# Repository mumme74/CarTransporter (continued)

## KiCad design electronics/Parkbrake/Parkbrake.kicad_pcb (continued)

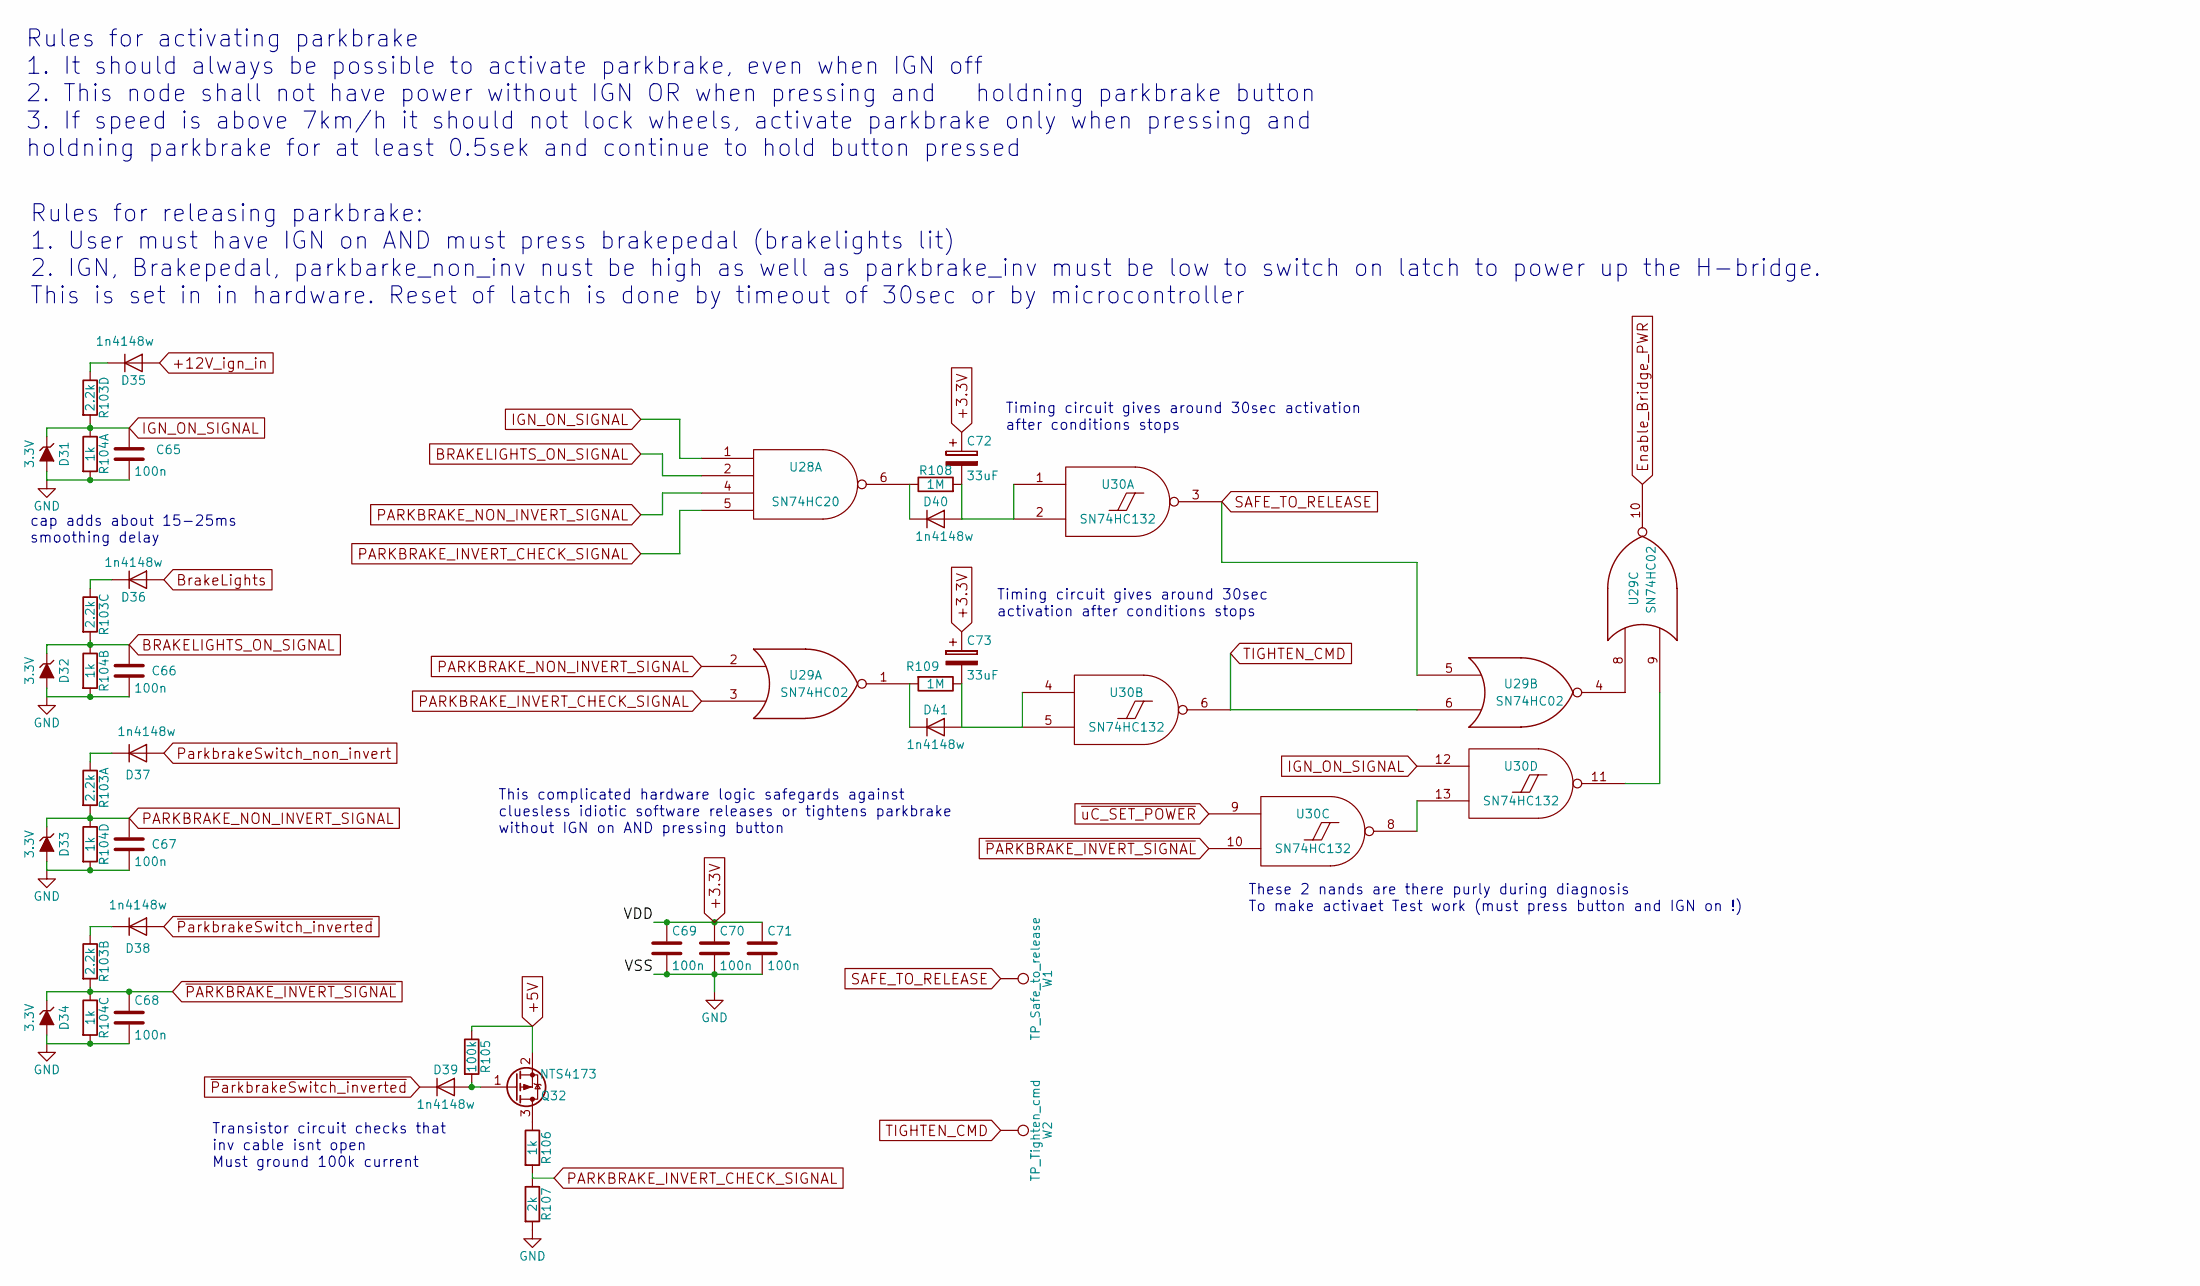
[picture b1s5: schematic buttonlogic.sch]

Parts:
C65, C66, C67, C68, C69, C70, C71: 100n; C_0805; part 0805B104J500CT; farnell 2496940
C72, C73: 33uF; CP_1206; part 293D336X96R3A2TE3; farnell 1754149
D31, D32, D33, D34: 3.3V; SOD-323; part MM3Z3V3ST1G; farnell 2463489
D35, D36, D37, D38, D39, D40, D41: 1n4148w; SOD-323; part 1N4148WS; farnell 1466524
Q32: NTS4173; SOT-323; part NTS4173PT1G; farnell 2533203
R103: 2.2k; R_Array_Concave_4x0603; part EXB38V222JV; farnell 2060102
R104: 1k; R_Array_Concave_4x0603; part EXB38V102JV; farnell 2060100
R105: 100k; R_0805; part MC01W08051100K; farnell 9332405
R106: 1k; R_0805; part MC01W080511K; farnell 9332383
R107: 2k; R_0805; part MC01W080512K; farnell 9332766
R108, R109: 1M; R_0805; part MC01W080511M; farnell 9332413
U28: SN74HC20; TSSOP-14_4.4x5mm_Pitch0.65mm; part SN74HC20PW; farnell 1741207
U29: SN74HC02; TSSOP-14_4.4x5mm_Pitch0.65mm; part SN74HC02PWR; farnell 9590927
U30: SN74HC132; TSSOP-14_4.4x5mm_Pitch0.65mm; part SN74HC132PWR; farnell 2342491
W1: TP_Safe_to_release; Measurement_Point_Round-SMD-Pad_Small
W2: TP_Tighten_cmd; Measurement_Point_Round-SMD-Pad_Small

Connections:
+3.3V: C69.1, C70.1, C71.1, C72.1, C73.1, U28.14 (VCC), U29.14 (VCC), U30.14 (VCC); also elsewhere on the board
+5V: Q32.2 (S), R105.1; also elsewhere on the board
+12V_ign_in: D35.2 (A); also elsewhere on the board
BRAKELIGHTS_ON_SIGNAL: C66.1, D32.1 (K), R103.6, R104.2, U28.2; also elsewhere on the board
BrakeLights: D36.2 (A); also elsewhere on the board
Enable_Bridge_PWR: U29.10; also elsewhere on the board
IGN_ON_SIGNAL: C65.1, D31.1 (K), R103.5, R104.1, U28.1, U30.12; also elsewhere on the board
LR_wheelsensor_in-: C65.2, C66.2, C67.2, C68.2, C69.2, C70.2, C71.2, D31.2 (A), D32.2 (A), D33.2 (A), D34.2 (A), R104.5, R104.6, R104.7, R104.8, R107.2, U28.7 (GND), U29.7 (GND), U30.7 (GND); also elsewhere on the board
unnamed: C72.2, D40.2 (A), R108.2, U30.1, U30.2
unnamed: C73.2, D41.2 (A), R109.1, U30.4, U30.5
unnamed: D35.1 (K), R103.4
unnamed: D36.1 (K), R103.3
unnamed: D37.1 (K), R103.1
unnamed: D38.1 (K), R103.2
unnamed: D39.2 (A), Q32.1 (G), R105.2
unnamed: D40.1 (K), R108.1, U28.6
unnamed: D41.1 (K), R109.2, U29.1
unnamed: Q32.3 (D), R106.1
unnamed: U29.4, U29.8
unnamed: U29.9, U30.11
unnamed: U30.8, U30.13
PARKBRAKE_INVERT_CHECK_SIGNAL: R106.2, R107.1, U28.5, U29.3
PARKBRAKE_NON_INVERT_SIGNAL: C67.1, D33.1 (K), R103.8, R104.4, U28.4, U29.2; also elsewhere on the board
ParkbrakeSwitch_non_invert: D37.2 (A); also elsewhere on the board
SAFE_TO_RELEASE: U29.5, U30.3, W1.1; also elsewhere on the board
TIGHTEN_CMD: U29.6, U30.6, W2.1; also elsewhere on the board
~PARKBRAKE_INVERT_SIGNAL: C68.1, D34.1 (K), R103.7, R104.3, U30.10; also elsewhere on the board
~ParkbrakeSwitch_inverted: D38.2 (A), D39.1 (K); also elsewhere on the board
~uC_SET_POWER: U30.9; also elsewhere on the board

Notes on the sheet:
Rules for activating parkbrake 1. It should always be possible to activate parkbrake, even when IGN off 2. This node shall not have power without IGN OR when pressing and holdning parkbrake button 3. If speed is above 7km/h it should not lock wheels, activate parkbrake only when pressing and holdni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
Rules for releasing parkbrake: 1. User must have IGN on AND must press brakepedal (brakelights lit) 2. IGN, Brakepedal, parkbarke_non_inv nust be high as well as parkbrake_inv must be low to switch on latch to power up the H-bridge. This is set in in hardware. Reset of latch is done by timeout of 3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
cap adds about 15-25ms smoothing delay
Transistor circuit checks that inv cable isnt open Must ground 100k current
Timing circuit gives around 30sec activation after conditions stops
Timing circuit gives around 30sec activation after conditions stops
This complicated hardware logic safegards against cluesless idiotic software releases or tightens parkbrake without IGN on AND pressing button
These 2 nands are there purly during diagnosis To make activaet Test work (must press button and IGN on !)

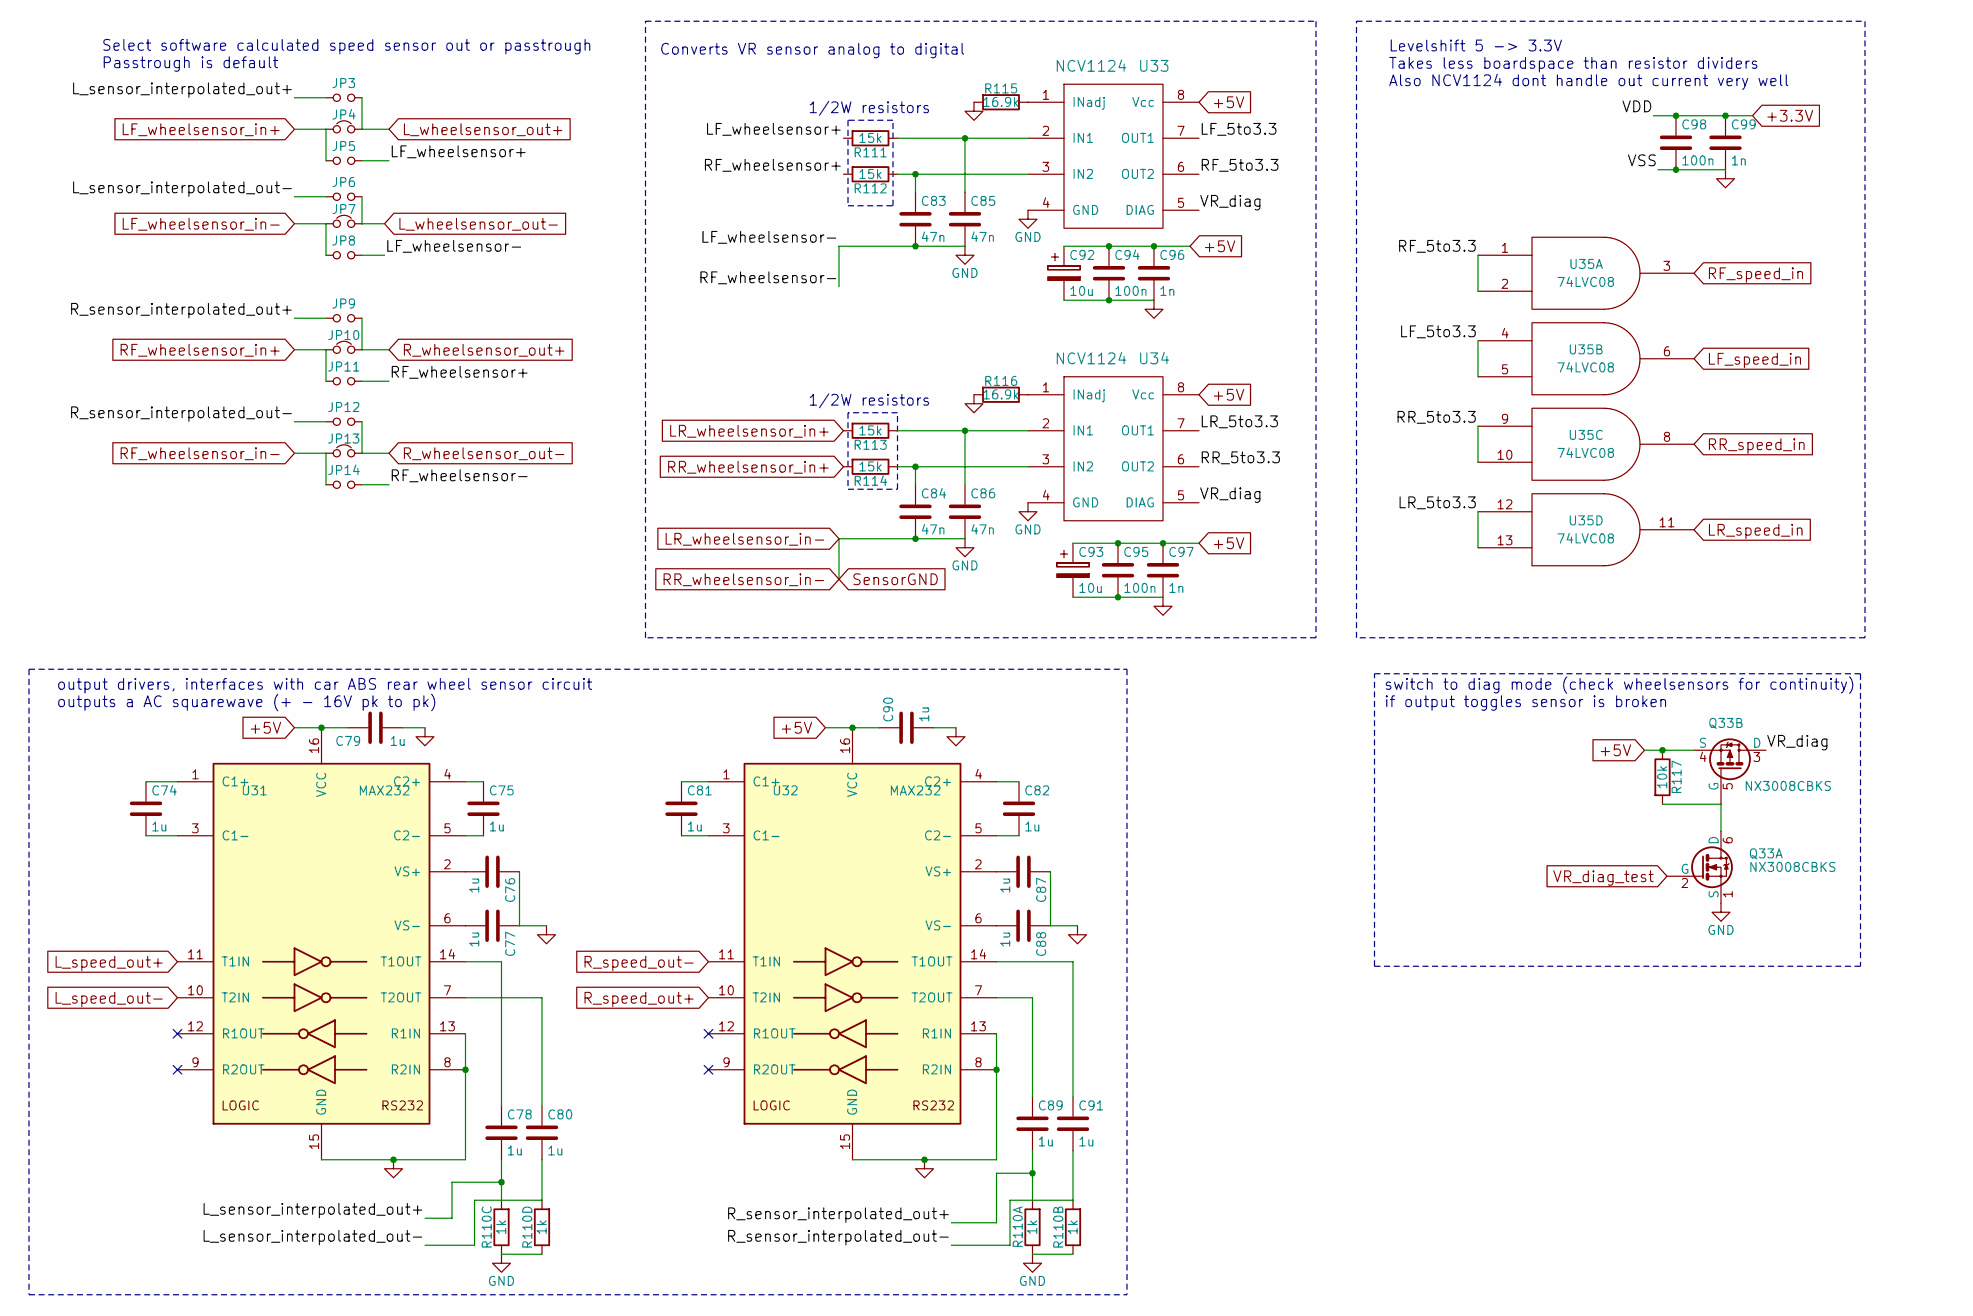
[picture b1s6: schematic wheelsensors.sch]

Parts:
C74, C75, C76, C77, C78, C79, C80, C81, C82, C87, C88, C89, C90, C91: 1u; C_1206; part GRM31MR71E105JA01L; farnell 2362126
C83, C84, C85, C86: 47n; C_0805; part 0805B473J500CT; farnell 2496981
C92, C93: 10u; CP_0805; part TMCP0J106KTRF; farnell 2491430
C94, C95, C98: 100n; C_0805; part 0805B104J500CT; farnell 2496940
C96, C97, C99: 1n; C_0805; part GRM2165C1H102JA01D; farnell 2494247
JP3: soft_L_out+; R_0805_HandSoldering; part RC1206JR-070RL; farnell 9240276
JP4: L_passth+; R_0805_HandSoldering; part RC1206JR-070RL; farnell 9240276
JP5: LF+_to_in; R_0805_HandSoldering; part RC1206JR-070RL; farnell 9240276
JP6: soft_L_out-; R_0805_HandSoldering; part RC1206JR-070RL; farnell 9240276
JP7: L_passth-; R_0805_HandSoldering; part RC1206JR-070RL; farnell 9240276
JP8: LF-_to_in; R_0805_HandSoldering; part RC1206JR-070RL; farnell 9240276
JP9: soft_R_out+; R_0805_HandSoldering; part RC1206JR-070RL; farnell 9240276
JP10: RF_passth+; R_0805_HandSoldering; part RC1206JR-070RL; farnell 9240276
JP11: RF+_to_in; R_0805_HandSoldering; part RC1206JR-070RL; farnell 9240276
JP12: soft_R_out-; R_0805_HandSoldering; part RC1206JR-070RL; farnell 9240276
JP13: RF_passth-; R_0805_HandSoldering; part RC1206JR-070RL; farnell 9240276
JP14: RF-_to_in; R_0805_HandSoldering; part RC1206JR-070RL; farnell 9240276
Q33: NX3008CBKS; SOT-363; part NX3008CBKS; farnell 2069539
R110: 1k; R_Array_Concave_4x0603; part EXB38V102JV; farnell 2060100
R111, R112, R113, R114: 15k; R_0805; part ERJP06F1502V; farnell 1750772
R115, R116: 16.9k; R_0805; part MC01W0805116K9; farnell 2141858
R117: 10k; R_0805; part MC01W0805110K; farnell 9332391
U31, U32: MAX232; TSSOP-16_4.4x5mm_Pitch0.65mm; part MAX202IPW; farnell 2335478
U33, U34: NCV1124; SOIC-8_3.9x4.9mm_Pitch1.27mm; part NCV1124DR2G; farnell 2534601
U35: 74LVC08; TSSOP-14_4.4x5mm_Pitch0.65mm; part 74LVC08APW-Q100.11; farnell 2445097

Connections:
+3.3V: C98.1, C99.1, U35.14 (VCC); also elsewhere on the board
+5V: C79.1, C90.1, C92.1, C93.1, C94.1, C95.1, C96.1, C97.1, Q33.4 (S), R117.1, U31.16 (VCC), U32.16 (VCC), U33.8 (Vcc), U34.8 (Vcc); also elsewhere on the board
/Wheelsensors/LF_5to3.3: U33.7 (OUT1), U35.4, U35.5
/Wheelsensors/LF_wheelsensor+: JP5.2, R111.2
/Wheelsensors/LR_5to3.3: U34.7 (OUT1), U35.12, U35.13
/Wheelsensors/L_sensor_interpolated_out+: C78.2, JP3.1, R110.6
/Wheelsensors/L_sensor_interpolated_out-: C80.2, JP6.1, R110.5
/Wheelsensors/RF_5to3.3: U33.6 (OUT2), U35.1, U35.2
/Wheelsensors/RF_wheelsensor+: JP11.2, R112.2
/Wheelsensors/RR_5to3.3: U34.6 (OUT2), U35.9, U35.10
/Wheelsensors/R_sensor_interpolated_out+: C89.2, JP9.1, R110.8
/Wheelsensors/R_sensor_interpolated_out-: C91.2, JP12.1, R110.7
/Wheelsensors/VR_diag: Q33.3 (D), U33.5 (DIAG), U34.5 (DIAG)
LF_speed_in: U35.6; also elsewhere on the board
LF_wheelsensor_in+: JP4.1, JP5.1; also elsewhere on the board
LF_wheelsensor_in-: JP7.1, JP8.1; also elsewhere on the board
LR_speed_in: U35.11; also elsewhere on the board
LR_wheelsensor_in+: R113.2; also elsewhere on the board
LR_wheelsensor_in-: C76.1, C77.1, C79.2, C83.2, C84.2, C85.2, C86.2, C87.1, C88.1, C90.2, C92.2, C93.2, C94.2, C95.2, C96.2, C97.2, C98.2, C99.2, JP8.2, JP14.2, Q33.1 (S), R110.1, R110.2, R110.3, R110.4, R115.2, R116.2, U31.8 (R2IN), U31.13 (R1IN), U31.15 (GND), U32.8 (R2IN), U32.13 (R1IN), U32.15 (GND), U33.4 (GND), U34.4 (GND), U35.7 (GND); also elsewhere on the board
L_speed_out+: U31.11 (T1IN); also elsewhere on the board
L_speed_out-: U31.10 (T2IN); also elsewhere on the board
L_wheelsensor_out+: JP3.2, JP4.2; also elsewhere on the board
L_wheelsensor_out-: JP6.2, JP7.2; also elsewhere on the board
unnamed: C74.1, U31.1 (C1+)
unnamed: C74.2, U31.3 (C1-)
unnamed: C75.1, U31.4 (C2+)
unnamed: C75.2, U31.5 (C2-)
unnamed: C76.2, U31.2 (VS+)
unnamed: C77.2, U31.6 (VS-)
unnamed: C78.1, U31.14 (T1OUT)
unnamed: C80.1, U31.7 (T2OUT)
unnamed: C81.1, U32.1 (C1+)
unnamed: C81.2, U32.3 (C1-)
unnamed: C82.1, U32.4 (C2+)
unnamed: C82.2, U32.5 (C2-)
unnamed: C83.1, R112.1, U33.3 (IN2)
unnamed: C84.1, R114.1, U34.3 (IN2)
unnamed: C85.1, R111.1, U33.2 (IN1)
unnamed: C86.1, R113.1, U34.2 (IN1)
unnamed: C87.2, U32.2 (VS+)
unnamed: C88.2, U32.6 (VS-)
unnamed: C89.1, U32.7 (T2OUT)
unnamed: C91.1, U32.14 (T1OUT)
unnamed: Q33.5 (G), Q33.6 (D), R117.2
unnamed: R115.1, U33.1 (INadj)
unnamed: R116.1, U34.1 (INadj)
RF_speed_in: U35.3; also elsewhere on the board
RF_wheelsensor_in+: JP10.1, JP11.1; also elsewhere on the board
RF_wheelsensor_in-: JP13.1, JP14.1; also elsewhere on the board
RR_speed_in: U35.8; also elsewhere on the board
RR_wheelsensor_in+: R114.2; also elsewhere on the board
R_speed_out+: U32.10 (T2IN); also elsewhere on the board
R_speed_out-: U32.11 (T1IN); also elsewhere on the board
R_wheelsensor_out+: JP9.2, JP10.2; also elsewhere on the board
R_wheelsensor_out-: JP12.2, JP13.2; also elsewhere on the board
VR_diag_test: Q33.2 (G); also elsewhere on the board

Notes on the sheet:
Select software calculated speed sensor out or passtrough Passtrough is default
1/2W resistors
output drivers, interfaces with car ABS rear wheel sensor circuit outputs a AC squarewave (+ - 16V pk to pk)
Converts VR sensor analog to digital
switch to diag mode (check wheelsensors for continuity) if output toggles sensor is broken
Levelshift 5 -> 3.3V Takes less boardspace than resistor dividers Also NCV1124 dont handle out current very well

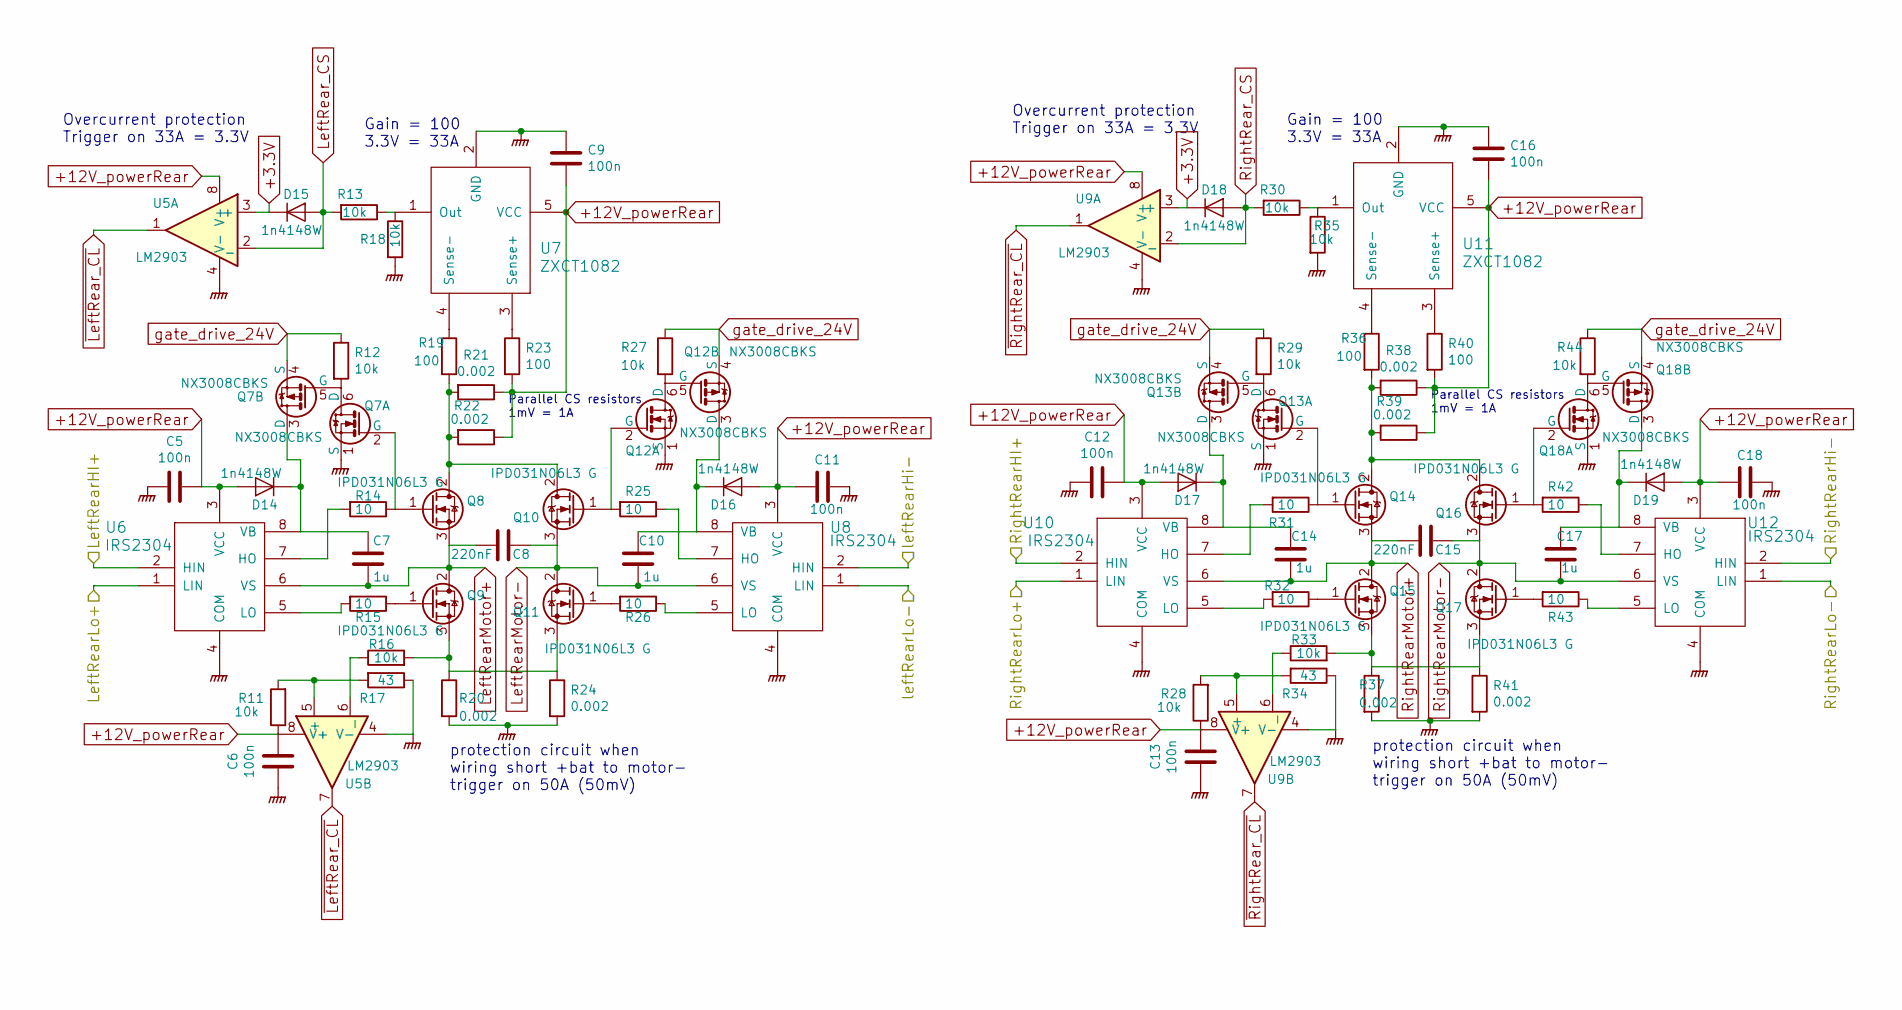
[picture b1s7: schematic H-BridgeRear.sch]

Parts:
C5, C6, C9, C11, C12, C13, C16, C18: 100n; C_0805; part 0805B104J500CT; farnell 2496940
C7, C10, C14, C17: 1u; C_1206; part GRM31MR71E105JA01L; farnell 2362126
C8, C15: 220nF; C_1206; part 1206B224J500CT; farnell 2497088
D14, D15, D16, D17, D18, D19: 1n4148W; SOD-323; part 1N4148WS; farnell 1466524
Q7, Q12, Q13, Q18: NX3008CBKS; SOT-363; part NX3008CBKS; farnell 2069539
Q8, Q9, Q10, Q11, Q14, Q15, Q16, Q17: IPD031N06L3 G; TO-252-2Lead; part IPD031N06L3 G; farnell 2480814
R11, R12, R13, R16, R18, R27, R28, R29, R30, R33, R35, R44: 10k; R_0805; part MC01W0805110K; farnell 9332391
R14, R15, R25, R26, R31, R32, R42, R43: 10; R_0805; part WF08P10R0FTL; farnell 2502783
R17, R34: 43; R_0805; part MC01W0805143R; farnell 9333240
R19, R23, R36, R40: 100; R_0805; part MC01W08051100R; farnell 9332375
R20, R21, R22, R24, R37, R38, R39, R41: 0.002; R_1206; part ULR1S-R002FT2; farnell 1621962
U5, U9: LM2903; TSSOP-8_4.4x3mm_Pitch0.65mm; part LM2903PT; farnell 1094243
U6, U8, U10, U12: IRS2304; SOIC-8_3.9x4.9mm_Pitch1.27mm; part IRS2304SPBF; farnell 1498208
U7, U11: ZXCT1082; SOT-23-5; part ZXCT1082E5TA; farnell 1904025

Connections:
+3.3V: D15.1 (K), D18.1 (K), U5.3 (+), U9.3 (+); also elsewhere on the board
+12V_powerRear: C5.1, C6.1, C9.2, C11.2, C12.1, C13.1, C16.2, C18.2, D14.2 (A), D16.2 (A), D17.2 (A), D19.2 (A), R11.1, R21.1, R22.1, R23.2, R28.1, R38.1, R39.1, R40.2, U5.8 (V+), U6.3 (VCC), U7.5 (VCC), U8.3 (VCC), U9.8 (V+), U10.3 (VCC), U11.5 (VCC), U12.3 (VCC); also elsewhere on the board
/H-Bridge_logic/H-BridgeRear/LeftRearHI+: U6.2 (HIN), U8.1 (LIN); also elsewhere on the board
/H-Bridge_logic/H-BridgeRear/LeftRearLo+: U6.1 (LIN), U8.2 (HIN); also elsewhere on the board
/H-Bridge_logic/H-BridgeRear/RightRearHI+: U10.2 (HIN), U12.1 (LIN); also elsewhere on the board
/H-Bridge_logic/H-BridgeRear/RightRearHi-: U10.1 (LIN), U12.2 (HIN); also elsewhere on the board
GNDPWR: C5.2, C6.2, C9.1, C11.1, C12.2, C13.2, C16.1, C18.1, Q7.1 (S), Q12.1 (S), Q13.1 (S), Q18.1 (S), R17.1, R18.2, R20.2, R24.2, R34.1, R35.2, R37.2, R41.2, U5.4 (V-), U6.4 (COM), U7.2 (GND), U8.4 (COM), U9.4 (V-), U10.4 (COM), U11.2 (GND), U12.4 (COM); also elsewhere on the board
LeftRearMotor+: C7.1, C8.2, Q8.3 (S), Q9.2 (D), U6.6 (VS); also elsewhere on the board
LeftRearMotor-: C8.1, C10.1, Q10.3 (S), Q11.2 (D), U8.6 (VS); also elsewhere on the board
LeftRear_CS: D15.2 (A), R13.2, U5.2 (_); also elsewhere on the board
unnamed: C7.2, D14.1 (K), Q7.3 (D), U6.8 (VB)
unnamed: C10.2, D16.1 (K), Q12.3 (D), U8.8 (VB)
unnamed: C14.2, D17.1 (K), Q13.3 (D), U10.8 (VB)
unnamed: C17.1, D19.1 (K), Q18.3 (D), U12.8 (VB)
unnamed: Q7.2 (G), Q8.1 (G), R14.1
unnamed: Q7.5 (G), Q7.6 (D), R12.2
unnamed: Q9.1 (G), R15.1
unnamed: Q10.1 (G), Q12.2 (G), R25.2
unnamed: Q8.2 (D), Q10.2 (D), R19.2, R21.2, R22.2
unnamed: Q11.1 (G), R26.2
unnamed: Q9.3 (S), Q11.3 (S), R16.2, R20.1, R24.1
unnamed: Q12.5 (G), Q12.6 (D), R27.2
unnamed: Q13.2 (G), Q14.1 (G), R31.1
unnamed: Q13.5 (G), Q13.6 (D), R29.2
unnamed: Q14.2 (D), Q16.2 (D), R36.2, R38.2, R39.2
unnamed: Q15.1 (G), R32.1
unnamed: Q15.3 (S), Q17.3 (S), R33.2, R37.1, R41.1
unnamed: Q16.1 (G), Q18.2 (G), R42.2
unnamed: Q17.1 (G), R43.2
unnamed: Q18.5 (G), Q18.6 (D), R44.2
unnamed: R11.2, R17.2, U5.5 (+)
unnamed: R13.1, R18.1, U7.1 (Out)
unnamed: R14.2, U6.7 (HO)
unnamed: R15.2, U6.5 (LO)
unnamed: R16.1, U5.6 (_)
unnamed: R19.1, U7.4 (Sense-)
unnamed: R23.1, U7.3 (Sense+)
unnamed: R25.1, U8.7 (HO)
unnamed: R26.1, U8.5 (LO)
unnamed: R28.2, R34.2, U9.5 (+)
unnamed: R30.1, R35.1, U11.1 (Out)
unnamed: R31.2, U10.7 (HO)
unnamed: R32.2, U10.5 (LO)
unnamed: R33.1, U9.6 (_)
unnamed: R36.1, U11.4 (Sense-)
unnamed: R40.1, U11.3 (Sense+)
unnamed: R42.1, U12.7 (HO)
unnamed: R43.1, U12.5 (LO)
RightRearMotor+: C14.1, C15.2, Q14.3 (S), Q15.2 (D), U10.6 (VS); also elsewhere on the board
RightRearMotor-: C15.1, C17.2, Q16.3 (S), Q17.2 (D), U12.6 (VS); also elsewhere on the board
RightRear_CS: D18.2 (A), R30.2, U9.2 (_); also elsewhere on the board
gate_drive_24V: Q7.4 (S), Q12.4 (S), Q13.4 (S), Q18.4 (S), R12.1, R27.1, R29.1, R44.1; also elsewhere on the board
~LeftRear_CL: U5.1, U5.7; also elsewhere on the board
~RightRear_CL: U9.1, U9.7; also elsewhere on the board

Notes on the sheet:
Parallel CS resistors 1mV = 1A
protection circuit when wiring short +bat to motor- trigger on 50A (50mV)
Gain = 100 3.3V = 33A
Overcurrent protection Trigger on 33A = 3.3V

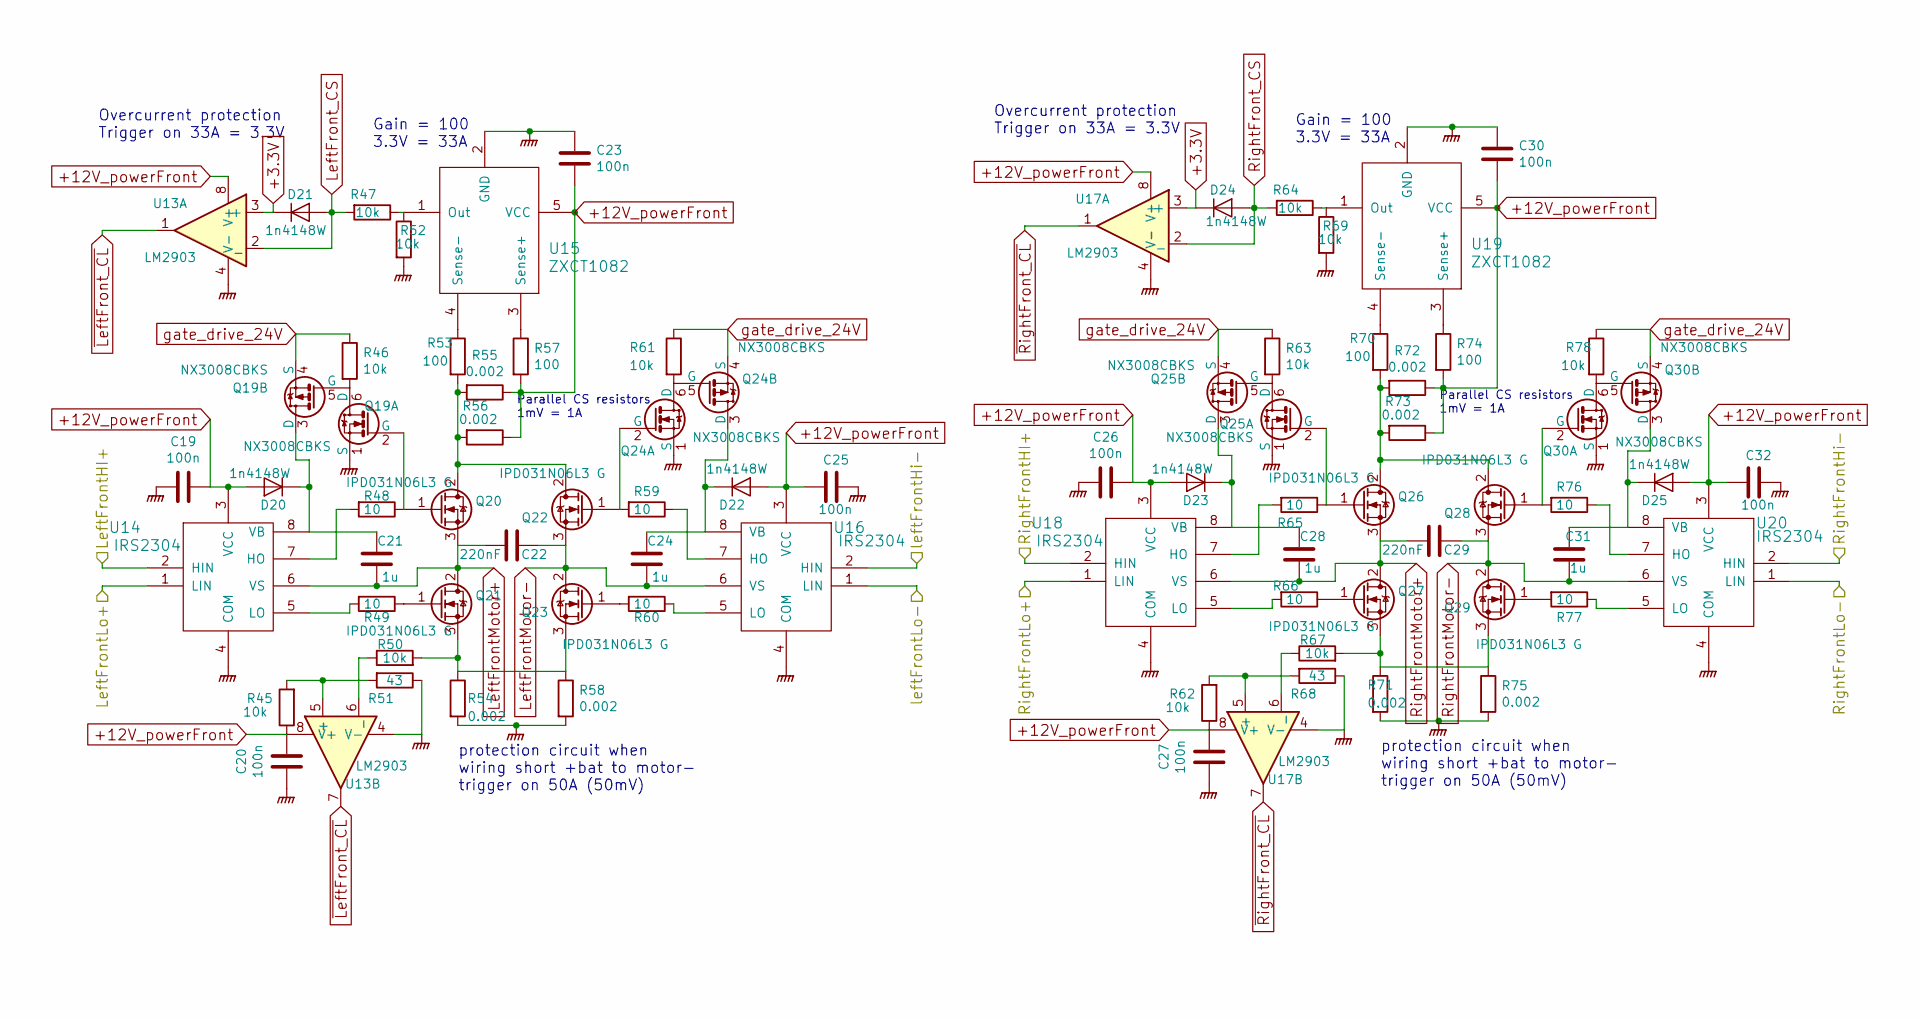
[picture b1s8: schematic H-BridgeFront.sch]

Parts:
C19, C20, C23, C25, C26, C27, C30, C32: 100n; C_0805; part 0805B104J500CT; farnell 2496940
C21, C24, C28, C31: 1u; C_1206; part GRM31MR71E105JA01L; farnell 2362126
C22, C29: 220nF; C_1206; part 1206B224J500CT; farnell 2497088
D20, D21, D22, D25: 1n4148W; SOD-323; part 1N4148WS; farnell 1466524
D23, D24: 1n4148W; SOD-323; part 1N4148WS; farnell 2433353
Q19, Q24, Q25, Q30: NX3008CBKS; SOT-363; part NX3008CBKS; farnell 2069539
Q20, Q21, Q22, Q23, Q26, Q27, Q28, Q29: IPD031N06L3 G; TO-252-2Lead; part IPD031N06L3 G; farnell 2480814
R45, R46, R47, R50, R52, R61, R62, R63, R64, R67, R69, R78: 10k; R_0805; part MC01W0805110K; farnell 9332391
R48, R49, R59, R60, R65, R66, R76, R77: 10; R_0805; part WF08P10R0FTL; farnell 2502783
R51, R68: 43; R_0805; part MC01W0805143R; farnell 9333240
R53, R57, R70, R74: 100; R_0805; part MC01W08051100R; farnell 9332375
R54, R55, R56, R58, R71, R72, R73, R75: 0.002; R_1206; part ULR1S-R002FT2; farnell 1621962
U13, U17: LM2903; TSSOP-8_4.4x3mm_Pitch0.65mm; part LM2903PT; farnell 1094243
U14, U16, U18, U20: IRS2304; SOIC-8_3.9x4.9mm_Pitch1.27mm; part IRS2304SPBF; farnell 1498208
U15, U19: ZXCT1082; SOT-23-5; part ZXCT1082E5TA; farnell 1904025

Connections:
+3.3V: D21.1 (K), D24.1 (K), U13.3 (+), U17.3 (+); also elsewhere on the board
+12V_powerFront: C19.1, C20.1, C23.2, C25.2, C26.1, C27.1, C30.2, C32.2, D20.2 (A), D22.2 (A), D23.2 (A), D25.2 (A), R45.1, R55.1, R56.1, R57.2, R62.1, R72.1, R73.1, R74.2, U13.8 (V+), U14.3 (VCC), U15.5 (VCC), U16.3 (VCC), U17.8 (V+), U18.3 (VCC), U19.5 (VCC), U20.3 (VCC); also elsewhere on the board
/H-Bridge_logic/H-BridgeFront/LeftFrontHI+: U14.2 (HIN), U16.1 (LIN); also elsewhere on the board
/H-Bridge_logic/H-BridgeFront/LeftFrontLo+: U14.1 (LIN), U16.2 (HIN); also elsewhere on the board
/H-Bridge_logic/H-BridgeFront/RightFrontHI+: U18.2 (HIN), U20.1 (LIN); also elsewhere on the board
/H-Bridge_logic/H-BridgeFront/RightFrontHi-: U18.1 (LIN), U20.2 (HIN); also elsewhere on the board
GNDPWR: C19.2, C20.2, C23.1, C25.1, C26.2, C27.2, C30.1, C32.1, Q19.1 (S), Q24.1 (S), Q25.1 (S), Q30.1 (S), R51.1, R52.2, R54.2, R58.2, R68.1, R69.2, R71.2, R75.2, U13.4 (V-), U14.4 (COM), U15.2 (GND), U16.4 (COM), U17.4 (V-), U18.4 (COM), U19.2 (GND), U20.4 (COM); also elsewhere on the board
LeftFrontMotor+: C21.1, C22.2, Q20.3 (S), Q21.2 (D), U14.6 (VS); also elsewhere on the board
LeftFrontMotor-: C22.1, C24.1, Q22.3 (S), Q23.2 (D), U16.6 (VS); also elsewhere on the board
LeftFront_CS: D21.2 (A), R47.2, U13.2 (_); also elsewhere on the board
unnamed: C21.2, D20.1 (K), Q19.3 (D), U14.8 (VB)
unnamed: C24.2, D22.1 (K), Q24.3 (D), U16.8 (VB)
unnamed: C28.2, D23.1 (K), Q25.3 (D), U18.8 (VB)
unnamed: C31.1, D25.1 (K), Q30.3 (D), U20.8 (VB)
unnamed: Q19.2 (G), Q20.1 (G), R48.1
unnamed: Q19.5 (G), Q19.6 (D), R46.2
unnamed: Q20.2 (D), Q22.2 (D), R53.2, R55.2, R56.2
unnamed: Q21.1 (G), R49.1
unnamed: Q21.3 (S), Q23.3 (S), R50.2, R54.1, R58.1
unnamed: Q22.1 (G), Q24.2 (G), R59.2
unnamed: Q23.1 (G), R60.2
unnamed: Q24.5 (G), Q24.6 (D), R61.2
unnamed: Q25.2 (G), Q26.1 (G), R65.1
unnamed: Q25.5 (G), Q25.6 (D), R63.2
unnamed: Q26.2 (D), Q28.2 (D), R70.2, R72.2, R73.2
unnamed: Q27.1 (G), R66.1
unnamed: Q27.3 (S), Q29.3 (S), R67.2, R71.1, R75.1
unnamed: Q28.1 (G), Q30.2 (G), R76.2
unnamed: Q29.1 (G), R77.2
unnamed: Q30.5 (G), Q30.6 (D), R78.2
unnamed: R45.2, R51.2, U13.5 (+)
unnamed: R47.1, R52.1, U15.1 (Out)
unnamed: R48.2, U14.7 (HO)
unnamed: R49.2, U14.5 (LO)
unnamed: R50.1, U13.6 (_)
unnamed: R53.1, U15.4 (Sense-)
unnamed: R57.1, U15.3 (Sense+)
unnamed: R59.1, U16.7 (HO)
unnamed: R60.1, U16.5 (LO)
unnamed: R62.2, R68.2, U17.5 (+)
unnamed: R64.1, R69.1, U19.1 (Out)
unnamed: R65.2, U18.7 (HO)
unnamed: R66.2, U18.5 (LO)
unnamed: R67.1, U17.6 (_)
unnamed: R70.1, U19.4 (Sense-)
unnamed: R74.1, U19.3 (Sense+)
unnamed: R76.1, U20.7 (HO)
unnamed: R77.1, U20.5 (LO)
RightFrontMotor+: C28.1, C29.2, Q26.3 (S), Q27.2 (D), U18.6 (VS); also elsewhere on the board
RightFrontMotor-: C29.1, C31.2, Q28.3 (S), Q29.2 (D), U20.6 (VS); also elsewhere on the board
RightFront_CS: D24.2 (A), R64.2, U17.2 (_); also elsewhere on the board
gate_drive_24V: Q19.4 (S), Q24.4 (S), Q25.4 (S), Q30.4 (S), R46.1, R61.1, R63.1, R78.1; also elsewhere on the board
~LeftFront_CL: U13.1, U13.7; also elsewhere on the board
~RightFront_CL: U17.1, U17.7; also elsewhere on the board

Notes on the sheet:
Parallel CS resistors 1mV = 1A
protection circuit when wiring short +bat to motor- trigger on 50A (50mV)
Gain = 100 3.3V = 33A
Overcurrent protection Trigger on 33A = 3.3V

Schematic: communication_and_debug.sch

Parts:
C57, C59, C60: 100n; C_0805; part 0805B104J500CT; farnell 2496940
C58: 1n; C_0805; part GRM2165C1H102JA01D; farnell 2494247
JP2: Jumper_NO_Small; R_0805_HandSoldering; part RC1206JR-070RL; farnell 9240276
P2: JTAG; Socket_Strip_Straight_1x08; part 61300811121; farnell 2356160
P3: UART; Socket_Strip_Straight_1x03; part 826629-3; farnell 3418297
R88, R90, R91, R94, R95, R96, R97: 10k; R_0805; part MC01W0805110K; farnell 9332391
R89: 120; R_0805; part MC01W08051120R; farnell 9332480
R92, R93: 330; R_0805; part MC01W08051330R; farnell 9333037
U26: SN65HVD1050D; SOIC-8_3.9x4.9mm_Pitch1.27mm; part SN65HVD1050D; farnell 1220984

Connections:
+3.3V: P2.1, R90.1, R91.1, R94.1, R95.1, R96.1, R97.1; also elsewhere on the board
+5V: C57.1, C58.1, JP2.2, U26.3 (Vcc); also elsewhere on the board
CAN_HI: R89.1, U26.7 (CANH); also elsewhere on the board
CAN_LO: R89.2, U26.6 (CANL); also elsewhere on the board
CAN_RX: U26.4 (RXD); also elsewhere on the board
CAN_TX: U26.1 (TXD); also elsewhere on the board
JTCLK: P2.3, R90.2; also elsewhere on the board
JTDI: P2.5, R94.2; also elsewhere on the board
JTDO: P2.4, R91.2; also elsewhere on the board
JTMS: P2.6, R95.2; also elsewhere on the board
JTNRST: P2.7, R96.2; also elsewhere on the board
LR_wheelsensor_in-: C57.2, C58.2, C59.2, C60.2, P2.2, P3.1, R88.1, U26.2 (GND); also elsewhere on the board
NRST: C60.1, P2.8, R97.2; also elsewhere on the board
unnamed: C59.1, U26.5 (Vref)
unnamed: JP2.1, R88.2, U26.8 (S)
unnamed: P3.2, R93.2
unnamed: P3.3, R92.1
USART_RX: R92.2; also elsewhere on the board
USART_TX: R93.1; also elsewhere on the board

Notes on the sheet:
CAN interface
bridge to run silent mode
Uses usart1 pins 42-3 because they're 5v tolerant
UART for debugging
JTAG port
Only termination resistor on endnodes

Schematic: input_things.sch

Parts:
C61, C62, C64: 100n; C_0805; part 0805B104J500CT; farnell 2496940
C63: 1n; C_0805; part GRM2165C1H102JA01D; farnell 2494247
D28, D29: 3.3V; SOD-323; part MM3Z3V3ST1G; farnell 2463489
D30: 1n4148w; SOD-323; part 1N4148WS; farnell 1466524
Q31: BSS138; SOT-323; part BSS138PW; farnell 1907611
R98, R100: 10k; R_0805; part MC01W0805110K; farnell 9332391
R99, R101: 1k; R_0805; part MC01W080511K; farnell 9332383
R102: 560; R_0805; part MC01W08051560R; farnell 9333363
U27: SN74LVC245ADBR; SSOP-20_5.3x7.2mm_Pitch0.65mm; part SN74LVC245ADBR; farnell 1595415

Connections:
+3.3V: C63.1, C64.1, U27.1 (OEa), U27.19 (OEb), U27.20 (VCC); also elsewhere on the board
+12V_Feed: D30.1 (K), R98.1; also elsewhere on the board
+12V_powerFront: R100.1; also elsewhere on the board
BRAKELIGHTS_ON_SIGNAL: U27.6 (I2a); also elsewhere on the board
BUTTON_INV_SIG: U27.16 (O1a); also elsewhere on the board
BUTTON_SIG: U27.18 (O0a); also elsewhere on the board
Enable_Bridge_PWR: U27.8 (I3a); also elsewhere on the board
Feed_voltsense: C61.1, D28.1 (K), R98.2, R99.1; also elsewhere on the board
IGN_ON_SIG: U27.9 (O0b); also elsewhere on the board
IGN_ON_SIGNAL: U27.11 (I0b); also elsewhere on the board
INDICATOR_ON: Q31.1 (G); also elsewhere on the board
LIGHTS_ON_SIG: U27.14 (O2a); also elsewhere on the board
LR_wheelsensor_in-: C61.2, C62.2, C63.2, C64.2, D28.2 (A), D29.2 (A), Q31.2 (S), R99.2, R101.2, U27.10 (GND); also elsewhere on the board
unnamed: D30.2 (A), Q31.3 (D), R102.2
PARKBRAKE_NON_INVERT_SIGNAL: U27.2 (I0a); also elsewhere on the board
PWR_ENABLED_SIG: U27.12 (O3a); also elsewhere on the board
PWR_voltsense: C62.1, D29.1 (K), R100.2, R101.1; also elsewhere on the board
Parkbrake_indicator_lamp: R102.1; also elsewhere on the board
RELEASE_CMD_SIG: U27.7 (O1b); also elsewhere on the board
SAFE_TO_RELEASE: U27.13 (I1b); also elsewhere on the board
TIGHTEN_CMD: U27.15 (I2b); also elsewhere on the board
TIGHTEN_CMD_SIG: U27.5 (O2b); also elsewhere on the board
~PARKBRAKE_INVERT_SIGNAL: U27.4 (I1a); also elsewhere on the board

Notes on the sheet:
This buffer prevents possibility for spurious software to activate power to the bridge Security reasons
Battery sense circuit NOTE! only measure when 12V power is activated
12V->1.2V 24V->2.4V max around 30v
IGN voltage sense circuit
Turns on (grounds) indicator LED
Diode is for ESD protection
